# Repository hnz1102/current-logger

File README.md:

<div align="center">
  <h1><code>Voltage-Current Logger</code></h1>
  
</div>

# Voltage-Current Logger - High-resolution digital power monitor and logger

This tool provides a logging function that gets data on voltage, current and power consumption. Voltage input range is from 0 to 85V, Maximum current input is 15A. 

# Feature

**High-resolution** - By using Texas Instruments INA228 IC - 20-bit delta-sigma ADC, It can be got measurement data with 195.uV Bus voltage and 163.84mV Shunt voltage. 

**Microcontroller on board** - No need for a client PC when you are measuring. Directly send to the server. 

**Transfer measurement data via WiFi** - This Logger can transfer data to Linux PC via WiFi network and you can see the dashboard graph in influxDB.

**Battery Powered** - Using LiPo battery. It can run for 24-48 hours.

**Multiple Adopter** - This Logger can be changed 4 type adopters (USB-Type-C-Type-C, USB-Type-A-mini Type-B, JST-PH-Connector for Battery, 3P-Terminal)  

# How to use the Logger
This logger has four types of adapters, and by changing them, it is possible to measure the usage voltage, current, and power consumption of various devices"

* Red Adapter - To measure the voltage and current from USB Type-C Power Adapter to Type-C Power Input Device(PCs, etc.)

* Yellow Adapter - To measure the voltage and current from USB Type mini-B port to USB Type-A output port.

* Green Adapter - To measure the voltage and current between JST-PH connector. (Batteries, etc.)

* Blue Adapter - To measure the voltage and current some cabling type.

For example, if you want to measure the voltage of USB-Type-C power, set the red adopter into the slot. If the power supply does not work, you can try to insert one of the connected Type-C connections in the opposite side of the back. Because a Type-C cable has two sides.

The Blue Adapter has 3 pins screw terminal. To measure voltage and current, connect to the following the schematic. 

DO NOT CONNECT WITH OPPOSITE POLARITY. IF CONNECTED, THE ADC IC IS WILL BE DAMAGED.

The measurement interval time can be selected from 5 ms to 1 sec. When the logger is powered on, the interval time is 5 ms, then pressing the INT button will set the interval to 10, 50, 100, 500ms, or 1 sec.
Push the START button, then the logger starts to send to the server voltage, current and power consumption data.

A display can show you the current voltage, current, power consumption, battery voltage, buffer consumption, and WiFi connection status.
If the WiFi Access Point cannot establish a connection, the display will not show WiFi mark. If voltage is measured while the WiFi is not connected, the data is stored in the logger's internal memory buffer. The buffer that is not being sent to the server is indicated by a red bar line on the display. When the buffer is full (the line reaches the right edge of the display), the measurement stops automatically. Then, when the WiFi is connected and transmitted to the server, the buffer line shrinks to the left. If the buffer is full and the measurement is stopped, pressing the Start button again discards the measurement data being held and starts the measurement again.

If you send data to the server, You can see the realtime data using Dashboard by [InfluxDB](https://www.influxdata.com/influxdb/).

After the measure, to stop logging, push the START button again.

To charge a battery, just connect to a USB Type-C port from the bus-powered USB port. During the charge, the CHG LED is RED ON. After the charging is full, the FUL LED is GREEN ON. And the charging will be stopped automatically. But, 

DO NOT CONTINUE THE CHARGE IF THE BATTERY IS FULL FOR A LONG TIME. 

# How to build from code and Install to the unit.

Using Ubuntu 22.04.03 LTS

1. Install Rust Compiler
```bash
$ sudo apt -y install git python3 python3-pip gcc build-essential curl pkg-config libudev-dev libtinfo5 clang libclang-dev llvm-dev udev
$ curl --proto '=https' --tlsv1.2 -sSf https://sh.rustup.rs | sh
select No.1
$ source "$HOME/.cargo/env"
```

2. Install toolchain for ESP32-C3
```bash
$ cargo install ldproxy
$ cargo install espup
$ rustup toolchain install nightly --component rust-src
$ rustup target add riscv32imc-unknown-none-elf
$ cargo install cargo-espflash
```

3. Add UDEV rules
```bash
$ sudo sh -c 'echo "SUBSYSTEMS==\"usb\", ATTRS{idVendor}==\"303a\", ATTRS{idProduct}==\"1001\", MODE=\"0666\"" > /etc/udev/rules.d/99-esp32.rules'
$ sudo udevadm control --reload-rules
$ sudo udevadm trigger
```

4. Download Current-Logger code
```bash
$ git clone https://github.com/hnz1102/current-logger.git
$ cd current-logger/src/current-logger
``` 
5. Setting WiFi SSID, Password, and InfluxDB server IP address.
```bash
src\current-logger\cfg.toml

[currentlogger]
wifi_ssid = "<your-AP-ssid>"     # Set your AP ssid.
wifi_psk = "<your-AP-Password>"  # Set password for ssid
http_server = "<PC address>:3001" # Set IP address and port. port should be 3001.
```

6. Connecting the board and Set device and set toolchain.
```bash
Connecting the current-Logger by USB to this build code PC. Then, 
$ cargo espflash board-info
select /dev/ttyACM0
Chip type:         esp32c3 (revision v0.4)
Crystal frequency: 40MHz
Flash size:        4MB
Features:          WiFi, BLE
MAC address:       xx:xx:xx:xx:xx:xx

$ rustup component add rust-src --toolchain nightly-2023-06-10-x86_64-unknown-linux-gnu
```

7. Build code and writing flash
```bash
$ cargo espflash flash --release --monitor
App/part. size:    964,240/3,145,728 bytes, 30.23%
[00:00:00] [========================================]      12/12      0x0                                                                       
[00:00:00] [========================================]       1/1       0x8000                                                                    
[00:00:11] [========================================]     546/546     0x10000                                                                   [2023-11-11T10:17:05Z INFO ] Flashing has completed!

And automaticaly boot!
```
# How to Install the influxDB and Agent

1. Download [influxDB](https://docs.influxdata.com/influxdb/v2.7/install/?t=Linux) and Install.
```bash
$ wget https://dl.influxdata.com/influxdb/releases/influxdb2-2.7.0-amd64.deb
$ sudo dpkg -i influxdb2-2.7.0-amd64.deb
$ sudo service influxdb start
```

2. Configure the influxDB

```
Connect to the 'http://<influxDB installed PC Address>:8086'
```
Click `GET STARTED` and set `Username`, `Password`, `Initial Organization Name`, and `Initial Bucket Name`
|Term|Value|
|---|---|
|Username|Set login username as influxDB administrator web console|
|Password|Set login password as influxDB administrator web console|
|Initial Organization Name| Organization Name ex. ORG|
|Initail Bucket Name| LOGGER |

After set them, click `CONTINUE`.

3. Copy the operator API token.

You can see the operator API token on the browser. YOU WON'T BE ABLE TO SEE IT AGAIN!
If you want to get new API token, click `API Tokens` menu form `Sources` Icon, then click `GENERATE API TOKEN` and select `All access token`, click `Save`.
You can see a new API token and get it.
After copy the token, click `CONFIGURE LATER`.

4. Import the Dashboard Template.

Click the `Dashboard` icon, and select `Import Dashboard` from the `CREATE DASHBOARD` menu.

Drop the `src/server/voltage_current_logger.json` file to `Drop a file here`, then click `IMPORT JSON AS DASHBOARD`.

You can see the `Voltage Current Logger Dashboard` pannel on the Dashboards page.

Click this panel, and You can see the Voltage-Current-Logger Dashboard.

If you want to customize the dashboard design, click configure mark. You can change the graph design.

5. Install the Agent.

Current-Logger can't directly send data to influxDB API since ESP32-C3 has not TSL software stack. This agent program is responsible for changing HTTP communication from Current-Logger to HTTPS communication and passing data to the InfluxDB API. This agent is purpose only for a local network because it has no security.

Before install you have to change parameters in main.js.

src/server/main.js
```javascript
const token = "<influxDB API Access Token>"
const url = 'http://<influxDB installed IP address>:8086'
let org = `<YOUR ORGANIZATION NAME: it has to be same the Initial Organization Name>`
let bucket = `LOGGER`
```

Install the agent program.

```bash
$ sudo apt install nodejs npm
$ cd src/server/
$ ./install.sh
```
If it is `Active: active` as shown below, it has started normally.
```
● influxdb-agent-current.service - InfluxDB Agent for Currentlogger
     Loaded: loaded (/lib/systemd/system/influxdb-agent-current.service; enabled; vendor preset: enabled)
     Active: active (running) since Sat 2023-11-11 11:36:02 UTC; 12ms ago
    Process: 6883 ExecStart=/var/lib/currentlogger/influxdb-agent-start.sh (code=exited, status=0/SUCCESS)
   Main PID: 6884 (node)
      Tasks: 1 (limit: 19009)
     Memory: 1.5M
        CPU: 10ms
     CGroup: /system.slice/influxdb-agent-current.service
             └─6884 /usr/bin/node /var/lib/currentlogger/main.js
```

6. Start Current-Logger Logging and Send Data.

Push the START button. Logging data will be sent to the influxDB. You can see the data on the dashboard.

## Schematic, PCB Gabar and Container 3D Data

There is a Schematic data in hardware directory include 3D printing data. 

## LICENSE
This source code is licensed under MIT. Other Hardware Schematic documents are licensed under CC-BY-SA V4.0.

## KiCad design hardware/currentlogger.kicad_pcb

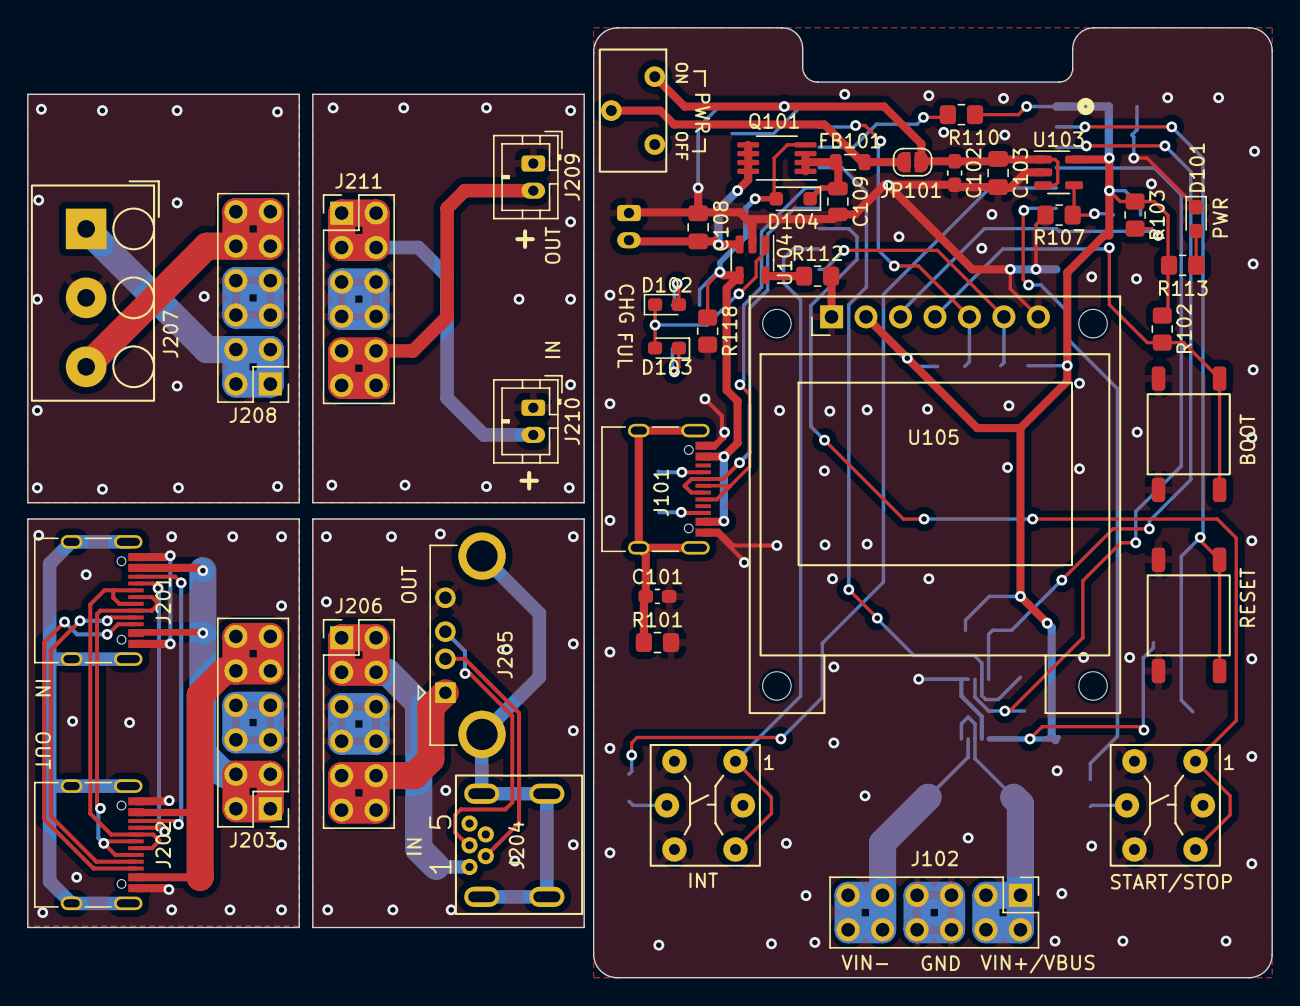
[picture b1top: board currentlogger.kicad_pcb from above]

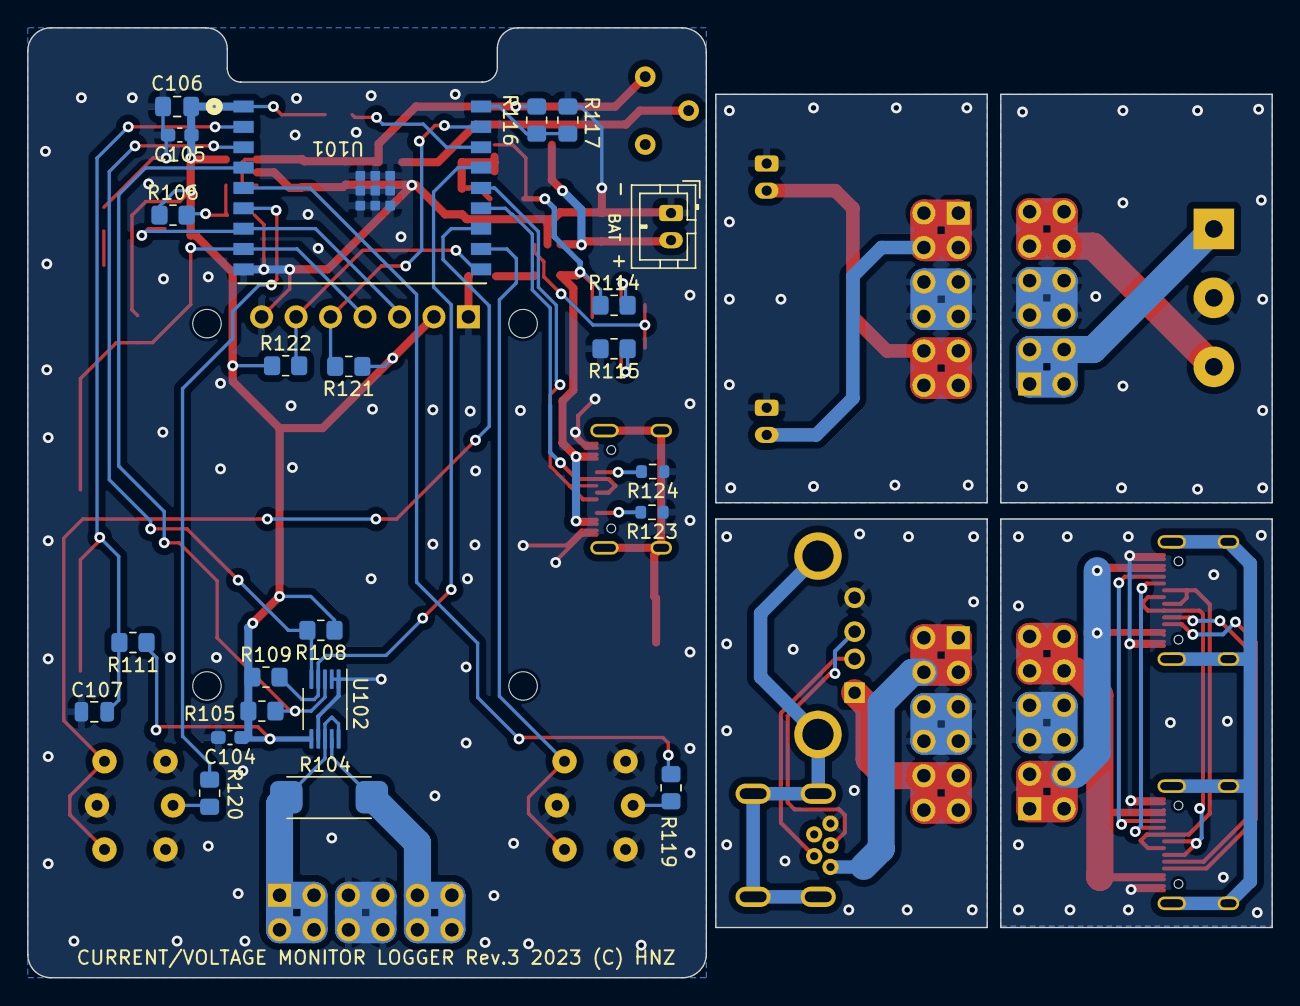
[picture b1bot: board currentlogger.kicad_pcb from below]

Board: 2 copper layers, 91.7 x 70.0 mm, 64 parts (23 on the bottom side), 58 nets.

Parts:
C101, C102, C104, C105: 0.1uF; C_0603_1608Metric_Pad1.08x0.95mm_HandSolder
C103, C106: 10uF; C_0805_2012Metric_Pad1.18x1.45mm_HandSolder
C107, C109: 1uF; C_0805_2012Metric
C108: 4.7uF; C_0805_2012Metric_Pad1.18x1.45mm_HandSolder
D101, D102: LED RED; LED_0603_1608Metric_Pad1.05x0.95mm_HandSolder
D103: LED GREEN; LED_0603_1608Metric_Pad1.05x0.95mm_HandSolder
D104: NSR0340HT1G; D_SOD-323_HandSoldering
FB101: BK2125HS601-T; L_0805_2012Metric
J101, J201, J202: USB_C_Receptacle_USB2.0_5077CR; USB_C_5077CR-16-SMC2-BK-TR
J102, J203, J206, J208, J211: PINOUT; PinHeader_2x06_P2.54mm_Vertical
J104: LiPo BATTERY; JST_PH_B2B-PH-K_1x02_P2.00mm_Vertical
J204: USB_B_Mini; usb mini B connector c2235 dim 2
J205: USB_A; USB_A_5075AR-04
J207: Screw_Terminal_01x03; TB112-2-2-3-E-1 Terminal Block
J209: BATTERY OUT JST_PH; JST_PH_B2B-PH-K_1x02_P2.00mm_Vertical
J210: BATTERY IN JST_PH; JST_PH_B2B-PH-K_1x02_P2.00mm_Vertical
JP101: SolderJumper_2_Open; SolderJumper-2_P1.3mm_Open_RoundedPad1.0x1.5mm
Q101: IRF7606PBF; MSOP-8_3x3mm_P0.65mm
R101, R102, R103, R105, R108, R109, R110, R111, R121, R122: 10K; R_0805_2012Metric_Pad1.20x1.40mm_HandSolder
R104: 10m; R_10mOHM
R106, R116, R117: 20K 1%; R_0805_2012Metric_Pad1.20x1.40mm_HandSolder
R107: 12K 1%; R_0805_2012Metric_Pad1.20x1.40mm_HandSolder
R112: 2K; R_0805_2012Metric_Pad1.20x1.40mm_HandSolder
R113: 1K; R_0805_2012Metric_Pad1.20x1.40mm_HandSolder
R114, R115, R119, R120: 330; R_0805_2012Metric_Pad1.20x1.40mm_HandSolder
R118: 100K; R_0805_2012Metric_Pad1.20x1.40mm_HandSolder
R123, R124: 5.1K; R_0603_1608Metric
SW101, SW102: TS-06104
SW103, SW104: SW_Push_LED; LS601-CU_CAP
SW105: SLIDE_SW; SLIDE_SW_IS1235-G
U101: ESP32-C3-WROOM-02-N4; IC18_ESP32-C3-WROOM-02-N4_EXP
U102: INA228; VSSOP-10_3x3mm_P0.5mm
U103: SPX3819M5-L; SOT-23-5
U104: MCP73831-2-OT; SOT-23-5
U105: SSD1331_DISPLAY; OLED SSD1331 SPI DISPLAY

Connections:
+3.3V: C104.1, C105.1, C106.1, R102.1, R103.1, R105.1, R106.1, R108.1, R109.1, R110.1, R111.1, R113.1, R121.1, R122.1, U101.1 (3V3), U102.6 (VS), U103.5 (OUT), U105.2 (VDD)
/Adopter/BAT-GND: J209.1, J210.1, J211.5, J211.6, J211.7, J211.8
/Adopter/TERMINAL-GND: J207.2, J208.5, J208.6, J208.7, J208.8
/Adopter/USB-A-VBUSOUT: J205.1 (VBUS), J206.9, J206.10, J206.11, J206.12
/Adopter/USB-AB-GND: J204.5 (GND), J205.4 (GND), J206.5, J206.6, J206.7, J206.8
/Adopter/USB-B-VBUSIN: J204.1 (VBUS), J206.1, J206.2, J206.3, J206.4
/Adopter/USB-C-GND: J201.A1 (GND), J201.A12 (GND), J201.B1 (GND), J201.B12 (GND), J202.A1 (GND), J202.A12 (GND), J202.B1 (GND), J202.B12 (GND), J203.5, J203.6, J203.7, J203.8
/Adopter/USB-C-VBUSIN: J201.A4 (VBUS), J201.A9 (VBUS), J201.B4 (VBUS), J201.B9 (VBUS), J203.1, J203.2, J203.3, J203.4
/Adopter/USB-C-VBUSOUT: J202.A4 (VBUS), J202.A9 (VBUS), J202.B4 (VBUS), J202.B9 (VBUS), J203.9, J203.10, J203.11, J203.12
/GPIO0: R116.2, R117.1, U101.18 (IO0)
/GPIO1: R121.2, U101.17 (IO1), U105.5 (~RES)
/GPIO2: R110.2, U101.16 (IO2)
/GPIO3: R109.2, U101.15 (IO3), U102.4 (SDA)
/GPIO4/TMS: R108.2, U101.3 (IO4), U102.5 (SCL)
/GPIO5/TDI: R105.2, U101.4 (IO5), U102.3 (~Alert)
/GPIO6/TCK: R119.2, U101.5 (IO6)
/GPIO7/TDO: R120.2, U101.6 (IO7)
/GPIO8: R103.2, U101.7 (IO8), U105.3 (SCLK)
/GPIO9: R102.2, SW101.A, SW101.B, U101.8 (IO9), U105.4 (SDIN)
/GPIO10: R122.2, U101.10 (IO10), U105.6 (D/C)
/RXD/GPIO20: SW103.1, SW103.2, U101.11 (RXD)
/TXD/GPIO21: SW104.1, SW104.2, U101.12 (TXD)
/USBDM: J101.A7 (D-), J101.B7 (D-), U101.13 (IO18)
/USBDP: J101.A6 (D+), J101.B6 (D+), U101.14 (IO19)
/USBVDD: D104.2 (A), J101.A4 (VBUS), J101.A9 (VBUS), J101.B4 (VBUS), J101.B9 (VBUS), Q101.4 (G), R114.1, R118.1, U104.4 (V_{DD})
/VBAT: C108.1, J104.2, Q101.5 (D), Q101.6 (D), Q101.7 (D), Q101.8 (D), U104.3 (V_{BAT})
/VIN: C102.1, C103.1, JP101.2 (B), R116.1, SW105.1 (A), U103.1 (IN), U103.3 (EN)
/VOUT: C109.1, D104.1 (K), FB101.1, Q101.1 (S), Q101.2 (S), Q101.3 (S)
/~RESET: C107.1, R111.2, SW102.A, SW102.B, U101.2 (EN)
GND: C101.2, C102.2, C103.2, C104.2, C105.2, C106.2, C107.2, C108.2, C109.2, D101.1 (K), J101.A1 (GND), J101.A12 (GND), J101.B1 (GND), J101.B12 (GND), J102.5, J102.6, J102.7, J102.8, J104.1, R101.2, R107.2, R112.2, R115.2, R117.2, R118.2, R123.1, R124.1, SW101.C, SW101.D, SW102.C, SW102.D, SW103.3, SW103.4, SW103.6 (K), SW104.3, SW104.4, SW104.6 (K), U101.9 (GND), U101.19 (GND), U101.20 (GND), U101.21 (GND), U101.22 (GND), U101.23 (GND), U101.24 (GND), U101.25 (GND), U101.26 (GND), U101.27 (GND), U102.1 (A1), U102.2 (A0), U102.7 (GND), U103.2 (GND), U104.2 (V_{SS}), U105.1 (VSS), U105.7 (~CS)
unnamed: D101.2 (A), R113.2
unnamed: D102.2 (A), R114.2
unnamed: D102.1 (K), D103.2 (A), U104.1 (STAT)
unnamed: D103.1 (K), R115.1
unnamed: J101.A5 (CC1), R124.2
unnamed: J101.B5 (CC2), R123.2
unnamed: C101.1, J101.S1 (SHIELD), R101.1
unnamed: J102.1, J102.2, J102.3, J102.4, R104.1, U102.8 (Vbus), U102.10 (Vin+)
unnamed: J102.9, J102.10, J102.11, J102.12, R104.2, U102.9 (Vin-)
unnamed: J201.A5 (CC1), J202.A5 (CC1)
unnamed: J201.B5 (CC2), J202.B5 (CC2)
unnamed: J201.A6 (D+), J201.B6 (D+), J202.A6 (D+), J202.B6 (D+)
unnamed: J201.A7 (D-), J201.B7 (D-), J202.A7 (D-), J202.B7 (D-)
unnamed: J201.A8 (SBU1), J202.A8 (SBU1)
unnamed: J201.B8 (SBU2), J202.B8 (SBU2)
unnamed: J201.S1 (SHIELD), J202.S1 (SHIELD)
unnamed: J204.3 (D+), J205.3 (D+)
unnamed: J204.2 (D-), J205.2 (D-)
unnamed: J204.6 (Shield), J205.5 (Shield)
unnamed: J207.1, J208.1, J208.2, J208.3, J208.4
unnamed: J207.3, J208.9, J208.10, J208.11, J208.12
unnamed: J209.2, J211.9, J211.10, J211.11, J211.12
unnamed: J210.2, J211.1, J211.2, J211.3, J211.4
unnamed: FB101.2, JP101.1 (A), SW105.2 (B)
unnamed: R119.1, SW103.5 (A)
unnamed: R120.1, SW104.5 (A)
unnamed: R106.2, R107.1, U103.4 (ADJ)
unnamed: R112.1, U104.5 (PROG)

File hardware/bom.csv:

Reference,Value,Footprint,Datasheet,distributor,Qty
"C101,C102,C104,C105",0.1uF,Capacitor_SMD:C_0603_1608Metric_Pad1.08x0.95mm_HandSolder,~,https://www.digikey.com/en/products/detail/yageo/CC0603ZRY5V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,4
"C103, C106",10uF,Capacitor_SMD:C_0805_2012Metric_Pad1.18x1.45mm_HandSolder,~,https://www.digikey.com/en/products/detail/murata-electronic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,2
"C107, C109",1uF,Capacitor_SMD:C_0805_2012Metric,~,https://www.digikey.com/en/products/detail/yageo/CC0805ZRY5V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,2
C108,4.7uF,Capacitor_SMD:C_0805_2012Metric_Pad1.18x1.45mm_HandSolder,~,https://www.digikey.com/en/products/detail/yageo/CC0805ZRY5V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,1
"D101, D102",LED RED,LED_SMD:LED_0603_1608Metric_Pad1.05x0.95mm_HandSolder,~,https://www.digikey.com/en/products/detail/harvatek-corporat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,2
D103,LED GREEN,LED_SMD:LED_0603_1608Metric_Pad1.05x0.95mm_HandSolder,~,https://www.digikey.com/en/products/detail/harvatek-corporat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,1
D104,NSR0340HT1G,Diode_SMD:D_SOD-323_HandSoldering,https://www.onsemi.com/pub/Collateral/NSR0340H-D.PDF,https://www.digikey.com/en/products/detail/onsemi/NSR0340HT1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,1
FB101,MH2029-601Y,Inductor_SMD:L_0805_2012Metric,~,https://www.digikey.com/en/products/detail/bourns-inc/MH2029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,1
"J101, J201, J202",USB4105-GF-A,Library:USB_C_5077CR-16-SMC2-BK-TR,https://www.usb.org/sites/default/files/documents/usb_type-c.zip,https://www.digikey.com/en/products/detail/gct/USB4105-GF-A/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,3
"J102, J203, J206, J208, J211",PINOUT,Connector_PinHeader_2.54mm:PinHeader_2x06_P2.54mm_Vertical,~,,5
J104,LiPo BATTERY,Connector_JST:JST_PH_B2B-PH-K_1x02_P2.00mm_Vertical,~,https://www.digikey.com/en/products/detail/jst-sales-america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,1
J204,USB_B_Mini,Library:usb mini B connector c2235 dim 2,~,https://akizukidenshi.com/catalog/g/gC-02235/,1
J205,USB_A,Library:USB_A_5075AR-04, ~,https://akizukidenshi.com/catalog/g/gC-00160/,1
J207,Screw_Terminal_01x03,Library:TB112-2-2-3-E-1 Terminal Block,~,https://akizukidenshi.com/catalog/g/gP-01310/,1
J209,BATTERY OUT JST_PH,Connector_JST:JST_PH_B2B-PH-K_1x02_P2.00mm_Vertical,~,https://www.digikey.com/en/products/detail/jst-sales-america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,1
J210,BATTERY IN JST_PH,Connector_JST:JST_PH_B2B-PH-K_1x02_P2.00mm_Vertical,~,https://www.digikey.com/en/products/detail/jst-sales-america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,1
JP101,SolderJumper_2_Open,Jumper:SolderJumper-2_P1.3mm_Open_RoundedPad1.0x1.5mm,~,,1
Q101,IRF7606TRPBF,Package_SO:MSOP-8_3x3mm_P0.65mm,http://www.irf.com/product-info/datasheets/data/irf7606pbf.pdf,https://www.digikey.com/en/products/detail/infineon-technolo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,1
"R101-R103, R105, R108-R111, R121, R122",10K,Resistor_SMD:R_0805_2012Metric_Pad1.20x1.40mm_HandSolder,~,https://www.digikey.jp/en/products/detail/yageo/RC0603JR-101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,10
R104,10m,Library:R_10mOHM,~,https://akizukidenshi.com/catalog/g/gP-01886/,1
"R106, R116, R117",20K 1%,Resistor_SMD:R_0805_2012Metric_Pad1.20x1.40mm_HandSolder,~,https://www.digikey.jp/en/products/detail/yageo/RC0603FR-072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,3
R107,12K 1%,Resistor_SMD:R_0805_2012Metric_Pad1.20x1.40mm_HandSolder,~,https://www.digikey.com/en/products/detail/yageo/RC0603FR-07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,1
R112,2K,Resistor_SMD:R_0805_2012Metric_Pad1.20x1.40mm_HandSolder,~,https://www.digikey.com/en/products/detail/yageo/RC0603JR-07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,1
R113,1K,Resistor_SMD:R_0805_2012Metric_Pad1.20x1.40mm_HandSolder,~,https://www.digikey.com/en/products/detail/yageo/RC0603FR-07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,1
"R114, R115, R119, R120",330,Resistor_SMD:R_0805_2012Metric_Pad1.20x1.40mm_HandSolder,~,https://www.digikey.com/en/products/detail/yageo/RC0603JR-13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,4
R118,100K,Resistor_SMD:R_0805_2012Metric_Pad1.20x1.40mm_HandSolder,~,https://www.digikey.com/en/products/detail/yageo/RC0603JR-07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,1
"R123, R124",5.1K,Resistor_SMD:R_0603_1608Metric,~,https://www.digikey.com/en/products/detail/yageo/RC0603JR-07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,2
"SW101, SW102",TS-06104,Library:TS-06104,,https://akizukidenshi.com/catalog/g/gP-15969/,2
SW103,SW_Push_LED_BLUE,Library:LS601-CU_CAP,~,https://akizukidenshi.com/catalog/g/gP-13871/,1
SW104,SW_Push_LED_RED,Library:LS601-CU_CAP,~,https://akizukidenshi.com/catalog/g/gP-13870/,1
SW105,SLIDE_SW,Library:SLIDE_SW_IS1235-G,~,https://akizukidenshi.com/catalog/g/gP-15368/,1
U101,ESP32-C3-WROOM-02-N4,Library:IC18_ESP32-C3-WROOM-02-N4_EXP,ESP32-C3-WROOM-02-N4,https://www.digikey.com/en/products/detail/espressif-systems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,1
U102,INA228,Package_SO:VSSOP-10_3x3mm_P0.5mm,http://www.ti.com/lit/ds/symlink/ina226.pdf,https://www.digikey.com/en/products/detail/texas-instruments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,1
U103,SPX3819M5-L,Package_TO_SOT_SMD:SOT-23-5,https://www.exar.com/content/document.ashx?id=22106&language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,https://www.digikey.com/en/products/detail/maxlinear-inc/SPX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,1
U104,MCP73831-2-OT,Package_TO_SOT_SMD:SOT-23-5,http://ww1.microchip.com/downloads/en/DeviceDoc/20001984g.pdf,https://www.digikey.com/en/products/detail/microchip-technol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,1
U105,SSD1331_DISPLAY,Library:OLED SSD1331 SPI DISPLAY,,https://akizukidenshi.com/catalog/g/gP-14435/,1

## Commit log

2023-11-11 Add Readme
2023-11-11 Add hardware data
2023-11-12 Update PCB data
2023-11-12 Battery voltage should be average.
2023-11-12 Interval time description is fiexed.
